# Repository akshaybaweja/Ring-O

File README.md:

# Ring-O

- [Code](./Code)
- [PCB Design Files](./PCB-Design-Files)
- [Photos](./Photos)
- [Major Project Report](Major_Report_Ring-O.pdf)
- [Product Video](https://www.youtube.com/watch?v=xZwoHolBt-g)

Read more about Ring-O on [Medium](http://medium.com/@akshaybaweja/ring-o-71918fd029cf)

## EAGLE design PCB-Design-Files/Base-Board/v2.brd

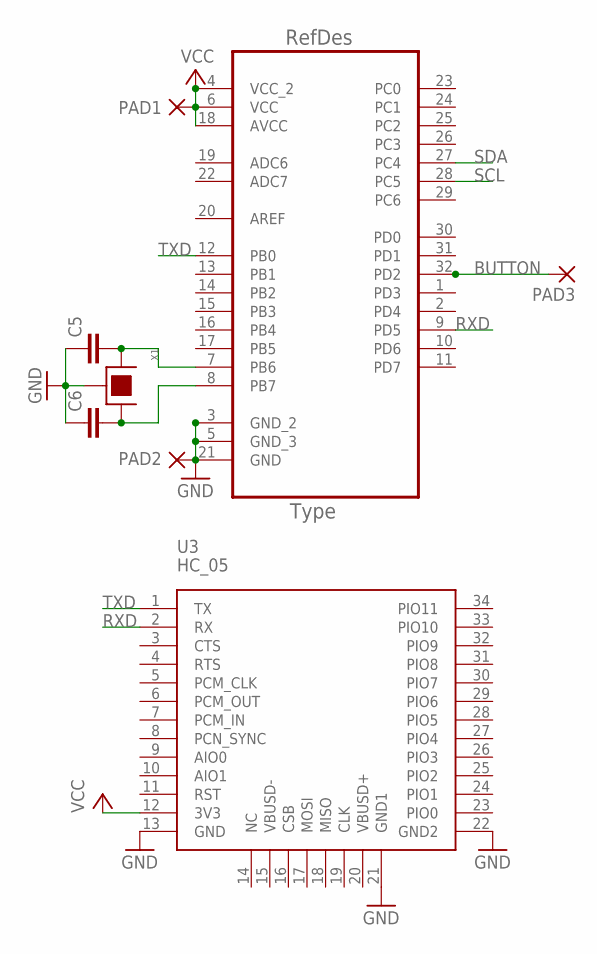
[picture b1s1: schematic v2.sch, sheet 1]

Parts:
C5, C6: C-EUC0402; C0402
PAD1, PAD2, PAD3: SMD2; SMD1,27-2,54
U2: ATMEGA328P-AU; QFP80P900X900X120-32N
U3: HC_05; BLUETOOTH_SMD
X1: SHIELDED_CRYSTAL_TSX-3225; TSX-3225

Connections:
BUTTON: PAD3.1, U2.32 (PD2)
GND: C5.1, C6.1, PAD2.1, U2.3 (GND_2), U2.5 (GND_3), U2.21 (GND), U3.13 (GND), U3.21 (GND1), U3.22 (GND2), X1.2, X1.4; also elsewhere on the board
unnamed: C5.2, U2.7 (PB6), X1.1
unnamed: C6.2, U2.8 (PB7), X1.3
RXD: U2.9 (PD5), U3.2 (RX)
SCL: U2.28 (PC5); also elsewhere on the board
SDA: U2.27 (PC4); also elsewhere on the board
TXD: U2.12 (PB0), U3.1 (TX)
VCC: PAD1.1, U2.4 (VCC_2), U2.6 (VCC), U2.18 (AVCC), U3.12 (3V3); also elsewhere on the board

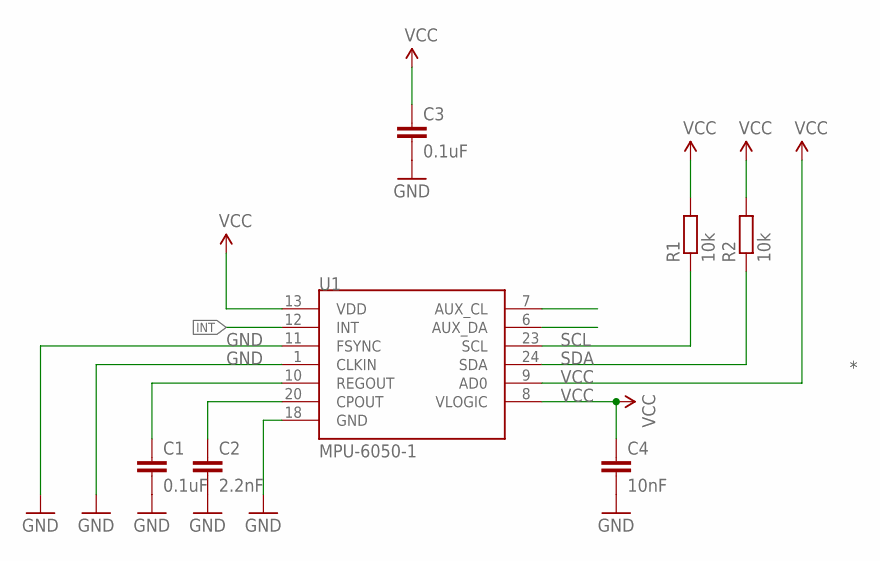
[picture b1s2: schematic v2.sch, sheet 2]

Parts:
C1, C3: 0.1uF; C0402
C2: 2.2nF; C0402
C4: 10nF; C0402
R1, R2: 10k; R0402
U1: MPU-6050-1; QFN-24-4MM2

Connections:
AUX_SCL: U1.7 (AUX_CL)
AUX_SDA: U1.6 (AUX_DA)
GND: C1.2, C2.2, C3.2, C4.2, U1.1 (CLKIN), U1.11 (FSYNC), U1.18 (GND); also elsewhere on the board
INT: U1.12 (INT)
unnamed: C2.1, U1.20 (CPOUT)
unnamed: C1.1, U1.10 (REGOUT)
SCL: R1.1, U1.23 (SCL); also elsewhere on the board
SDA: R2.1, U1.24 (SDA); also elsewhere on the board
VCC: C3.1, C4.1, R1.2, R2.2, U1.8 (VLOGIC), U1.9 (AD0), U1.13 (VDD); also elsewhere on the board

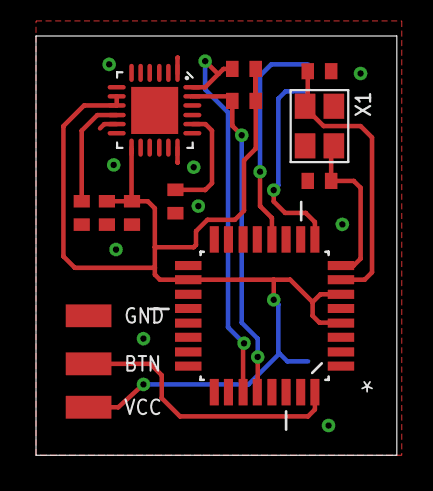
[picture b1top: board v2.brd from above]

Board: 2 copper layers, 20.0 x 23.3 mm, 15 parts (1 on the bottom side), 11 nets.

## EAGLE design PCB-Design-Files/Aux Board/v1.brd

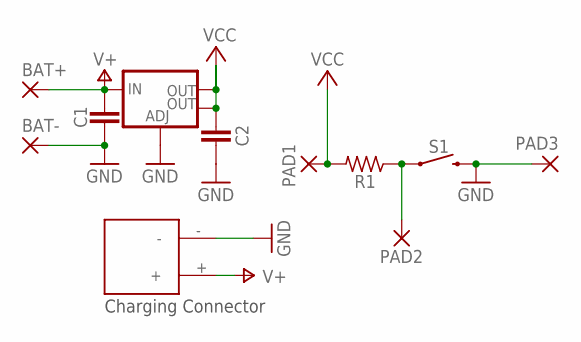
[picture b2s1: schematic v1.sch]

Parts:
BAT+: SMD2; SMD1,27-2,54
BAT-: SMD2; SMD1,27-2,54
C1, C2: C-EUC0402; C0402
PAD1, PAD2, PAD3: SMD2; SMD1,27-2,54
R1: R-US_R0402; R0402
S1: MOMENTARY-SWITCH-SPST-PTH-6.0MM; TACTILE_SWITCH_PTH_6.0MM
U1: V_REG_LM1117SOT223; SOT223
U$1: JST-JST-2

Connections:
GND: BAT-.1, C1.1, C2.1, PAD3.1, S1.3 (2), U1.1 (ADJ), U$1.-
unnamed: PAD2.1, R1.1, S1.1
V+: BAT+.1, C1.2, U1.3 (IN), U$1.+
VCC: C2.2, PAD1.1, R1.2, U1.2 (OUT), U1.4 (OUT)

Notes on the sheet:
Charging Connector

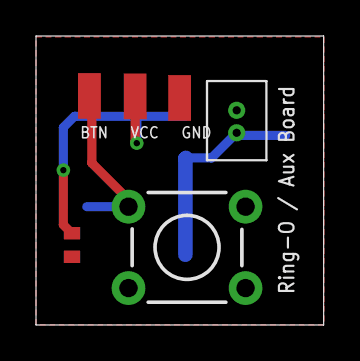
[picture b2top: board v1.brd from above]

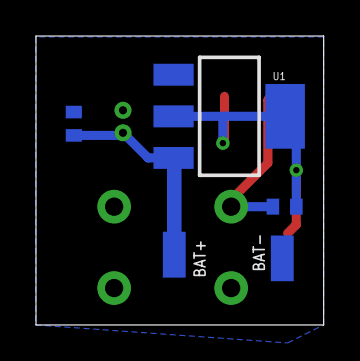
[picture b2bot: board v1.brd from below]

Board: 2 copper layers, 16.0 x 16.1 mm, 11 parts (5 on the bottom side), 4 nets.

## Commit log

2018-05-11 commit #2
2018-05-11 commit #3
2018-05-11 commit #4
2018-05-11 added keyboard
2018-05-12 added GUI Functionality
2018-05-15 final commit before presentation
2018-05-17 added new gestures
2020-08-15 restructuring

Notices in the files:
parts and their libraries:
SparkFun-Switches: Licensing: Creative Commons ShareAlike 4.0 International - https://creativecommons.org/licenses/by-sa/4.0
